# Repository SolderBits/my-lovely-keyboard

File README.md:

# My Lovely Keyboard

My Lovely Keyboard is a custom 75% mechanical keyboard with a hot-swap MX PCB,  rotary encoders with push buttons, and 3D-printed parts. The build pairs Akko Creamy Cyan clicky switches with SoulCat Cowgirl keycaps for the extra girly touch.

## PCB

The design uses a Pro Micro nRF52840 development board, four 74HC595 shift registers, and 1N4148 switching diodes for the key matrix. Jerrzi MX hot-swap sockets let you swap individual switches without desoldering them.

The hardware plan also includes a single-cell LiPo with a TP4056 charging module.

### Schematic and Board layout

### PCB renders

## Case

The build includes 3D-printed parts and SSS Fourwrap V2 PCB screw-in stabilizers. The stabilizer kit includes four 2U wires and wires for both 6.25U and 7U spacebars.

## Bill of Materials

| Part | Purpose | Purchase quantity | Total (INR) | Total (USD, approx.) |
|---|---|---:|---:|---:|
| [Akko Creamy Cyan switches](https://stackskb.com/store/akko-creamy-cyan-switch-pack-of-45-pre-order/) | Clicky MX switches | 2 packs of 45 | ₹2,598.00 | $28.00 |
| [Jerrzi MX hot-swap sockets](https://neomacro.in/products/jerrzi-mx-hotswap-sockets) | Removable switch mounting | 9 packs of 10 | ₹450.00 | $4.85 |
| [Pro Micro nRF52840](https://robu.in/product/promicro-nrf52840-development-board/) | Main controller | 1 | ₹899.00 | $9.69 |
| [74HC595 shift register](https://robocraze.com/products/8-bit-serial-to-parallel-shift-register-ic-74hc595) | Expand digital outputs | 4 | ₹60.00 | $0.65 |
| [3.7 V 10,000 mAh LiPo](https://makerbazar.in/products/single-cell-3-7v-10000mah-lipo-battery) | Battery power, variant without BMS or wires | 1 | ₹349.00 | $3.76 |
| [TP4056 1 A module](https://makerbazar.in/products/tp4056-1a-li-ion-lithium-battery-charging-module?variant=45459125567728) | Single-cell charging | 1 | ₹18.00 | $0.19 |
| [Hongyan EC11H rotary encoders](https://robu.in/product/hongyan-ec11h-7ce20p1zy15f7-rotary-encoder-with-push-button-switch-vertical-plug-in-5-pin/) | Rotary and push-button inputs | 2 | ₹116.00 | $1.25 |
| [SS-12D00 1P2T slide switches](https://robu.in/product/1-month-warranty-255/) | Slide switches | 6 | ₹11.34 | $0.12 |
| [SSS Fourwrap V2 stabilizers](https://neomacro.in/products/sss-fourwrap-v2-stabilizers) | Support wider keys | 1 kit | ₹1,059.00 | $11.41 |
| [PCB fabrication](https://jlcpcb.com/) | Custom keyboard PCB | 1 order | ₹3,692.77 | $39.80 |
| [1N4148 switching diodes](https://robu.in/product/1n4148-1w-zener-diode-pack-of-50/) | Key matrix isolation | 120 | ₹128.00 | $1.38 |
| [SoulCat Cowgirl keycaps](https://neomacro.in/products/soulcat-cowgirl-keycaps-pre-order) | 141-piece MOA-profile PBT keycap set | 1 set | ₹2,039.00 | $21.97 |
| 3D-printed parts | Mechanical assembly |  | |  |
| **Shipping ** | | | **₹119.81** | **$1.29** |
| **Total ** | | | **₹11,539.92** | **$124.37** |

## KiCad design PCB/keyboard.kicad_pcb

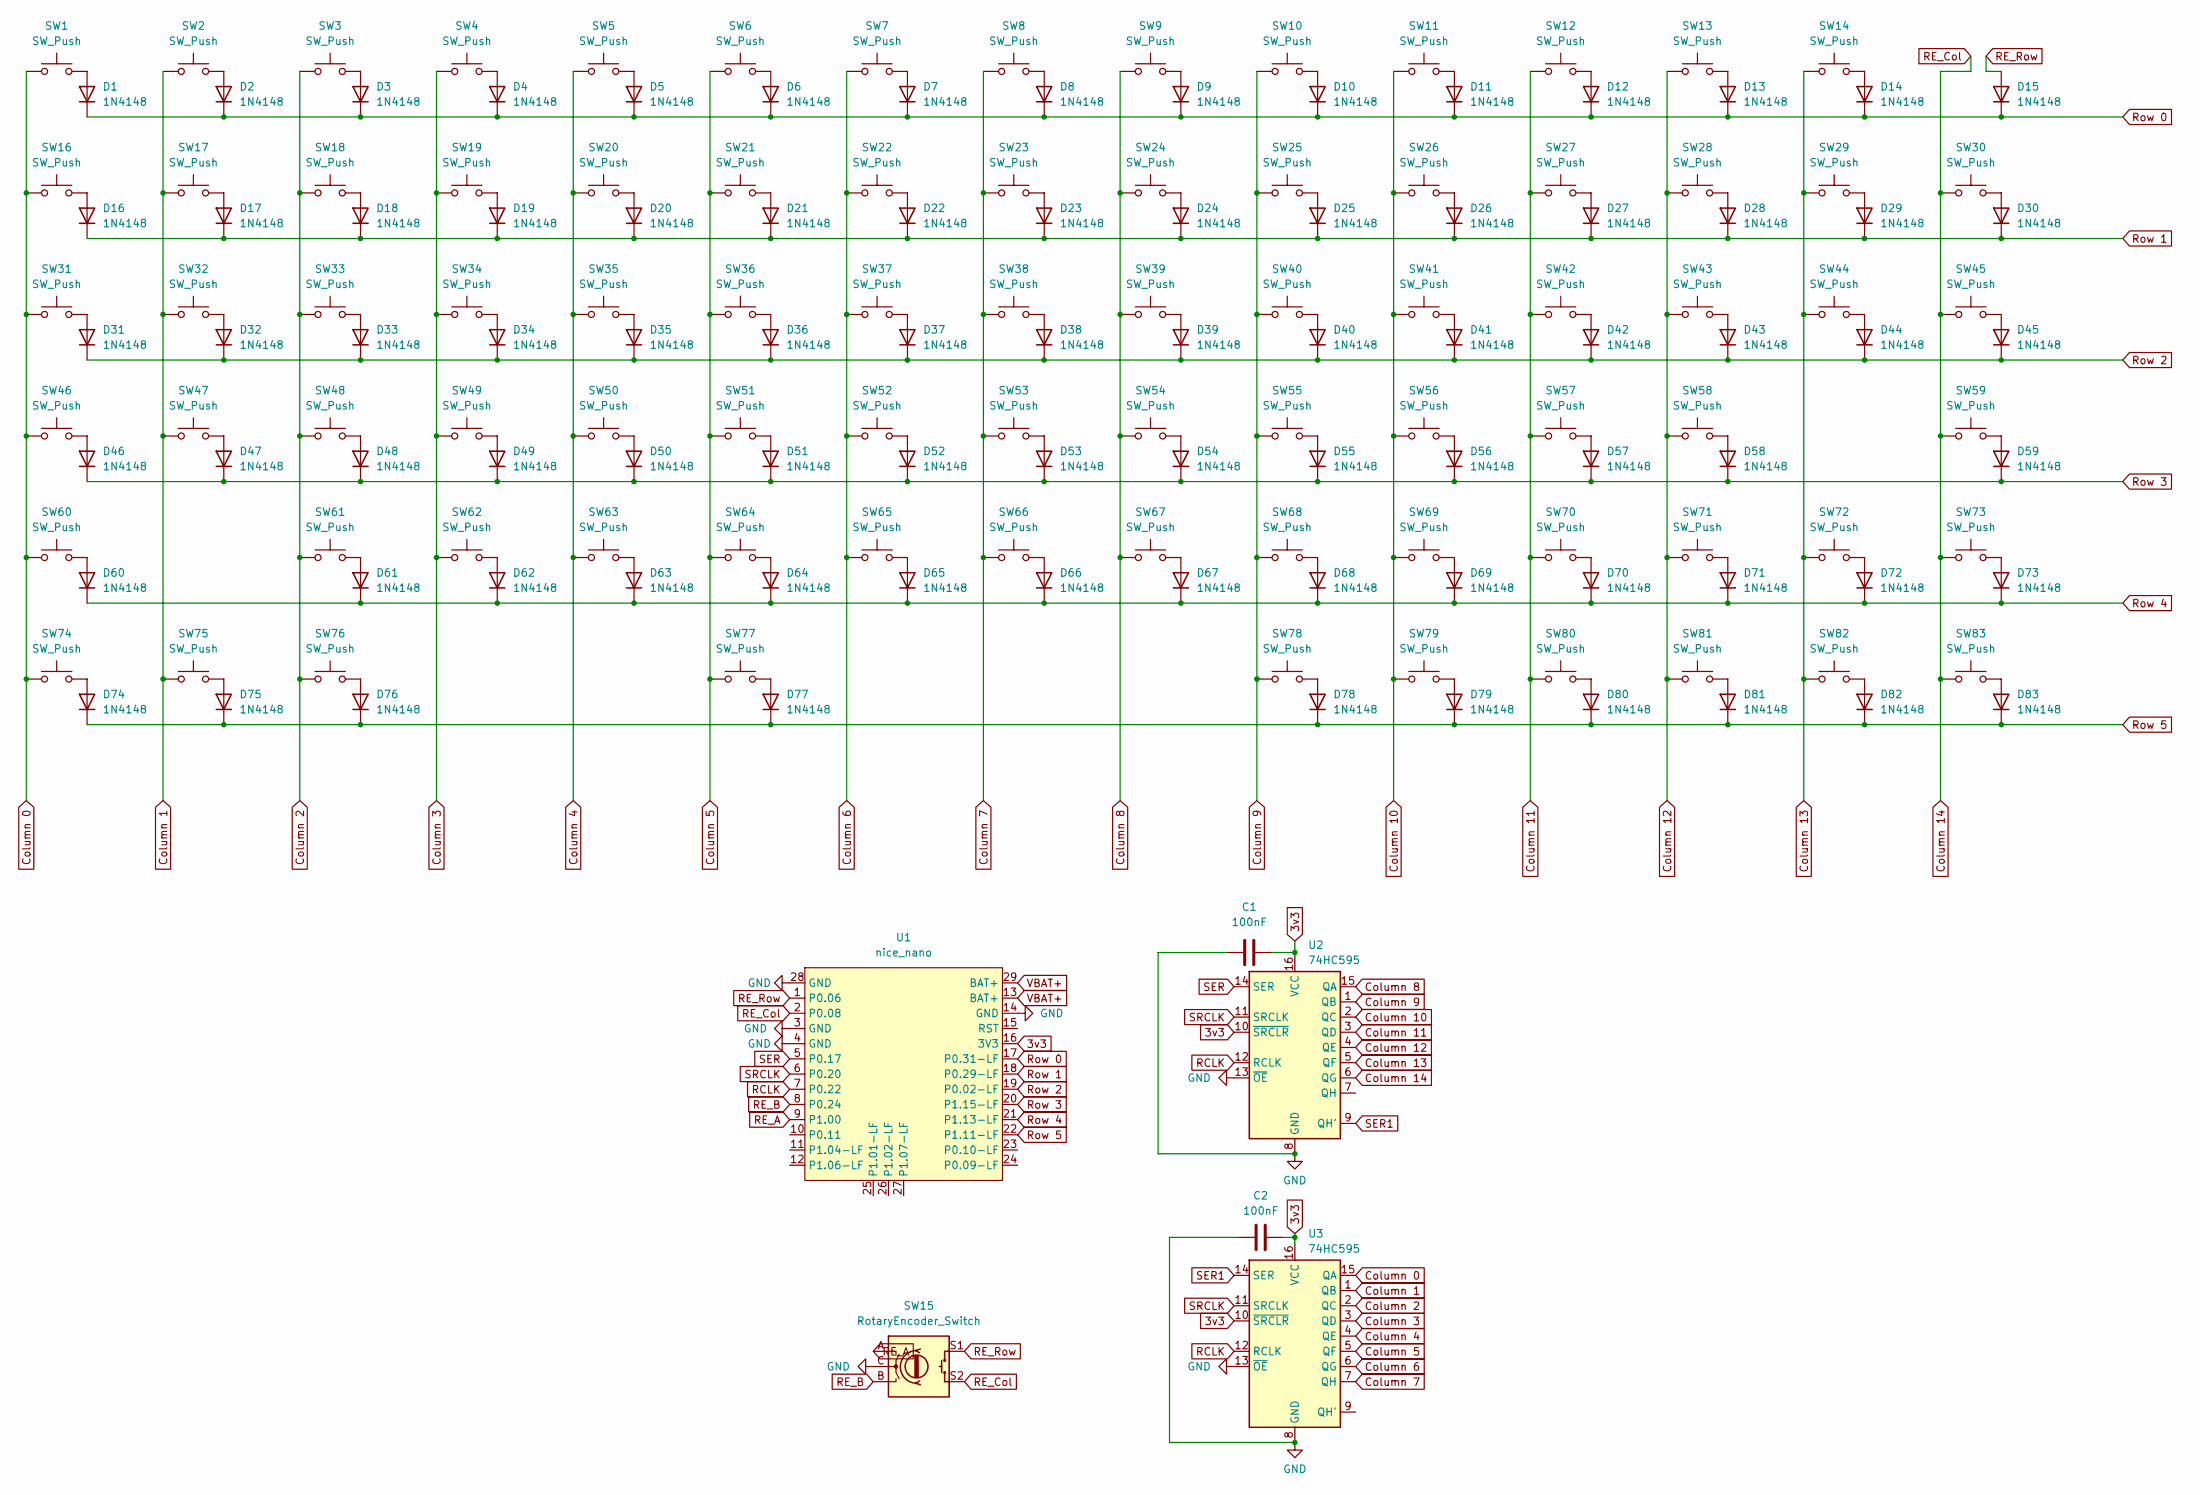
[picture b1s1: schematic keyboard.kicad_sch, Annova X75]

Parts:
C1, C2: 100nF; C_Disc_D3.0mm_W1.6mm_P2.50mm
D1, D2, D3, D4, D5, D6, D7, D8, D9, D10, D11, D12, D13, D14, D15, D16, D17, D18, D19, D20, D21, D22, D23, D24, D25, D26, D27, D28, D29, D30, D31, D32, D33, D34, D35, D36, D37, D38, D39, D40, D41, D42, D43, D44, D45, D46, D47, D48, D49, D50, D51, D52, D53, D54, D55, D56, D57, D58, D59, D60, D61, D62, D63, D64, D65, D66, D67, D68, D69, D70, D71, D72, D73, D74, D75, D76, D77, D78, D79, D80, D81, D82, D83: 1N4148; D_DO-35_SOD27_P7.62mm_Horizontal
SW1, SW2, SW3, SW4, SW5, SW6, SW7, SW8, SW9, SW10, SW11, SW12, SW13, SW14, SW16, SW17, SW18, SW19, SW20, SW21, SW22, SW23, SW24, SW25, SW26, SW27, SW28, SW30, SW32, SW33, SW34, SW35, SW36, SW37, SW38, SW39, SW40, SW41, SW42, SW43, SW45, SW47, SW48, SW49, SW50, SW51, SW52, SW53, SW54, SW55, SW56, SW57, SW59, SW61, SW62, SW63, SW64, SW65, SW66, SW67, SW68, SW69, SW70, SW72, SW73, SW78, SW79, SW80, SW81, SW82, SW83: SW_Push; SW_Hotswap_Kailh_MX_Plated_1.00u_With_Switch
SW15: RotaryEncoder_Switch; Encoder_EC11_MX_Combo
SW29: SW_Push; SW_Hotswap_Kailh_MX_Plated_2.00u_With_Switch
SW31, SW44: SW_Push; SW_Hotswap_Kailh_MX_Plated_1.50u_With_Switch
SW46, SW71: SW_Push; SW_Hotswap_Kailh_MX_Plated_1.75u_With_Switch
SW58, SW60: SW_Push; SW_Hotswap_Kailh_MX_Plated_2.25u_With_Switch
SW74, SW75, SW76: SW_Push; SW_Hotswap_Kailh_MX_Plated_1.25u_With_Switch
SW77: SW_Push; SW_Hotswap_Kailh_MX_Plated_6.25u_With_Switch
U1: nice_nano; SuperMini NRF52840
U2, U3: 74HC595; DIP-16_W7.62mm

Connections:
3v3: C1.1, C2.1, U1.16 (3V3), U2.10 (~SRCLR), U2.16 (VCC), U3.10 (~SRCLR), U3.16 (VCC)
Column 0: SW1.1, SW16.1, SW31.1, SW46.1, SW60.1, SW74.1, U3.15 (QA)
Column 1: SW2.1, SW17.1, SW32.1, SW47.1, SW75.1, U3.1 (QB)
Column 2: SW3.1, SW18.1, SW33.1, SW48.1, SW61.1, SW76.1, U3.2 (QC)
Column 3: SW4.1, SW19.1, SW34.1, SW49.1, SW62.1, U3.3 (QD)
Column 4: SW5.1, SW20.1, SW35.1, SW50.1, SW63.1, U3.4 (QE)
Column 5: SW6.1, SW21.1, SW36.1, SW51.1, SW64.1, SW77.1, U3.5 (QF)
Column 6: SW7.1, SW22.1, SW37.1, SW52.1, SW65.1, U3.6 (QG)
Column 7: SW8.1, SW23.1, SW38.1, SW53.1, SW66.1, U3.7 (QH)
Column 8: SW9.1, SW24.1, SW39.1, SW54.1, SW67.1, U2.15 (QA)
Column 9: SW10.1, SW25.1, SW40.1, SW55.1, SW68.1, SW78.1, U2.1 (QB)
Column 10: SW11.1, SW26.1, SW41.1, SW56.1, SW69.1, SW79.1, U2.2 (QC)
Column 11: SW12.1, SW27.1, SW42.1, SW57.1, SW70.1, SW80.1, U2.3 (QD)
Column 12: SW13.1, SW28.1, SW43.1, SW58.1, SW71.1, SW81.1, U2.4 (QE)
Column 13: SW14.1, SW29.1, SW44.1, SW72.1, SW82.1, U2.5 (QF)
Column 14: SW15.S2, SW30.1, SW45.1, SW59.1, SW73.1, SW83.1, U1.2 (P0.08), U2.6 (QG)
GND: C1.2, C2.2, SW15.C, U1.3 (GND), U1.4 (GND), U1.14 (GND), U1.28 (GND), U2.8 (GND), U2.13 (~OE), U3.8 (GND), U3.13 (~OE)
unnamed: D1.2 (A), SW1.2
unnamed: D2.2 (A), SW2.2
unnamed: D3.2 (A), SW3.2
unnamed: D4.2 (A), SW4.2
unnamed: D5.2 (A), SW5.2
unnamed: D6.2 (A), SW6.2
unnamed: D7.2 (A), SW7.2
unnamed: D8.2 (A), SW8.2
unnamed: D9.2 (A), SW9.2
unnamed: D10.2 (A), SW10.2
unnamed: D11.2 (A), SW11.2
unnamed: D12.2 (A), SW12.2
unnamed: D13.2 (A), SW13.2
unnamed: D14.2 (A), SW14.2
unnamed: D16.2 (A), SW16.2
unnamed: D17.2 (A), SW17.2
unnamed: D18.2 (A), SW18.2
unnamed: D19.2 (A), SW19.2
unnamed: D20.2 (A), SW20.2
unnamed: D21.2 (A), SW21.2
unnamed: D22.2 (A), SW22.2
unnamed: D23.2 (A), SW23.2
unnamed: D24.2 (A), SW24.2
unnamed: D25.2 (A), SW25.2
unnamed: D26.2 (A), SW26.2
unnamed: D27.2 (A), SW27.2
unnamed: D28.2 (A), SW28.2
unnamed: D29.2 (A), SW29.2
unnamed: D30.2 (A), SW30.2
unnamed: D31.2 (A), SW31.2
unnamed: D32.2 (A), SW32.2
unnamed: D33.2 (A), SW33.2
unnamed: D34.2 (A), SW34.2
unnamed: D35.2 (A), SW35.2
unnamed: D36.2 (A), SW36.2
unnamed: D37.2 (A), SW37.2
unnamed: D38.2 (A), SW38.2
unnamed: D39.2 (A), SW39.2
unnamed: D40.2 (A), SW40.2
unnamed: D41.2 (A), SW41.2
unnamed: D42.2 (A), SW42.2
unnamed: D43.2 (A), SW43.2
unnamed: D44.2 (A), SW44.2
unnamed: D45.2 (A), SW45.2
unnamed: D46.2 (A), SW46.2
unnamed: D47.2 (A), SW47.2
unnamed: D48.2 (A), SW48.2
unnamed: D49.2 (A), SW49.2
unnamed: D50.2 (A), SW50.2
unnamed: D51.2 (A), SW51.2
unnamed: D52.2 (A), SW52.2
unnamed: D53.2 (A), SW53.2
unnamed: D54.2 (A), SW54.2
unnamed: D55.2 (A), SW55.2
unnamed: D56.2 (A), SW56.2
unnamed: D57.2 (A), SW57.2
unnamed: D58.2 (A), SW58.2
unnamed: D59.2 (A), SW59.2
unnamed: D60.2 (A), SW60.2
unnamed: D61.2 (A), SW61.2
unnamed: D62.2 (A), SW62.2
unnamed: D63.2 (A), SW63.2
unnamed: D64.2 (A), SW64.2
unnamed: D65.2 (A), SW65.2
unnamed: D66.2 (A), SW66.2
unnamed: D67.2 (A), SW67.2
unnamed: D68.2 (A), SW68.2
unnamed: D69.2 (A), SW69.2
unnamed: D70.2 (A), SW70.2
unnamed: D71.2 (A), SW71.2
unnamed: D72.2 (A), SW72.2
unnamed: D73.2 (A), SW73.2
unnamed: D74.2 (A), SW74.2
unnamed: D75.2 (A), SW75.2
unnamed: D76.2 (A), SW76.2
unnamed: D77.2 (A), SW77.2
unnamed: D78.2 (A), SW78.2
unnamed: D79.2 (A), SW79.2
unnamed: D80.2 (A), SW80.2
unnamed: D81.2 (A), SW81.2
unnamed: D82.2 (A), SW82.2
unnamed: D83.2 (A), SW83.2
RCLK: U1.7 (P0.22), U2.12 (RCLK), U3.12 (RCLK)
RE_A: SW15.A, U1.9 (P1.00)
RE_B: SW15.B, U1.8 (P0.24)
RE_Row: D15.2 (A), SW15.S1, U1.1 (P0.06)
Row 0: D1.1 (K), D2.1 (K), D3.1 (K), D4.1 (K), D5.1 (K), D6.1 (K), D7.1 (K), D8.1 (K), D9.1 (K), D10.1 (K), D11.1 (K), D12.1 (K), D13.1 (K), D14.1 (K), D15.1 (K), U1.17 (P0.31-LF)
Row 1: D16.1 (K), D17.1 (K), D18.1 (K), D19.1 (K), D20.1 (K), D21.1 (K), D22.1 (K), D23.1 (K), D24.1 (K), D25.1 (K), D26.1 (K), D27.1 (K), D28.1 (K), D29.1 (K), D30.1 (K), U1.18 (P0.29-LF)
Row 2: D31.1 (K), D32.1 (K), D33.1 (K), D34.1 (K), D35.1 (K), D36.1 (K), D37.1 (K), D38.1 (K), D39.1 (K), D40.1 (K), D41.1 (K), D42.1 (K), D43.1 (K), D44.1 (K), D45.1 (K), U1.19 (P0.02-LF)
Row 3: D46.1 (K), D47.1 (K), D48.1 (K), D49.1 (K), D50.1 (K), D51.1 (K), D52.1 (K), D53.1 (K), D54.1 (K), D55.1 (K), D56.1 (K), D57.1 (K), D58.1 (K), D59.1 (K), U1.20 (P1.15-LF)
Row 4: D60.1 (K), D61.1 (K), D62.1 (K), D63.1 (K), D64.1 (K), D65.1 (K), D66.1 (K), D67.1 (K), D68.1 (K), D69.1 (K), D70.1 (K), D71.1 (K), D72.1 (K), D73.1 (K), U1.21 (P1.13-LF)
Row 5: D74.1 (K), D75.1 (K), D76.1 (K), D77.1 (K), D78.1 (K), D79.1 (K), D80.1 (K), D81.1 (K), D82.1 (K), D83.1 (K), U1.22 (P1.11-LF)
SER: U1.5 (P0.17), U2.14 (SER)
SER1: U2.9 (QH'), U3.14 (SER)
SRCLK: U1.6 (P0.20), U2.11 (SRCLK), U3.11 (SRCLK)
VBAT+: U1.13 (BAT+), U1.29 (BAT+)

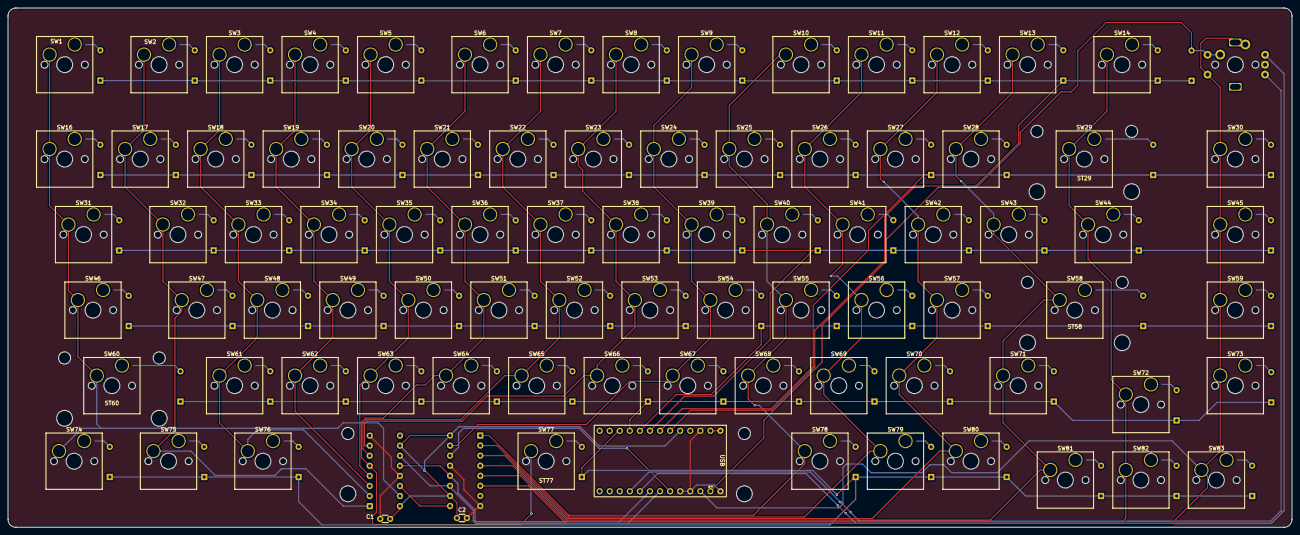
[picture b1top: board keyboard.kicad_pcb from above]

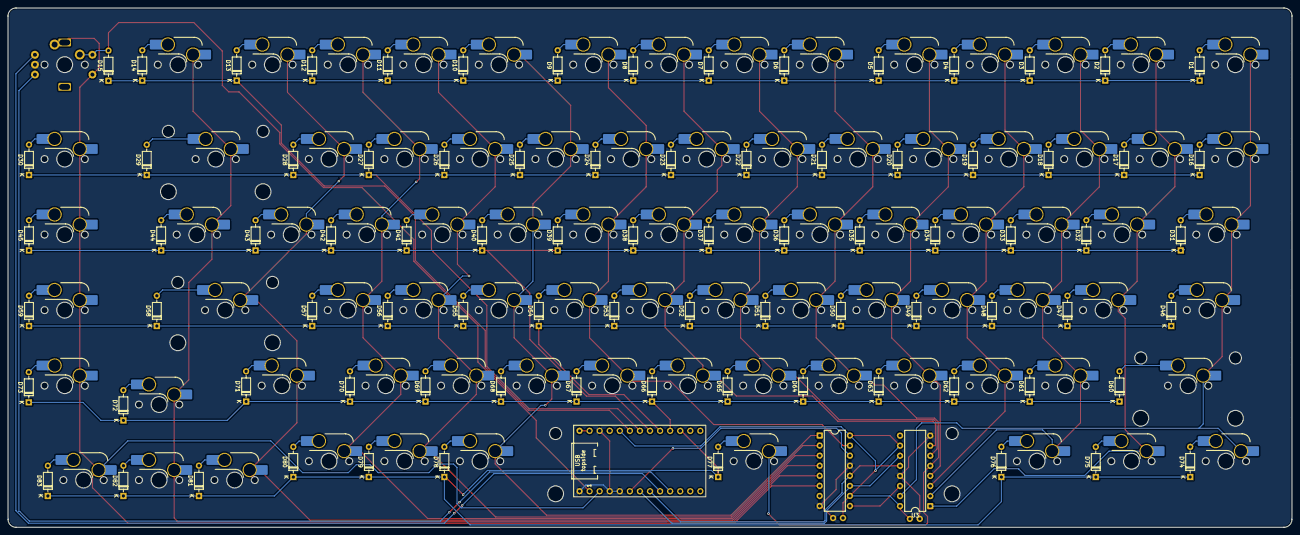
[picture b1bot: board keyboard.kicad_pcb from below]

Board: 2 copper layers, 323.9 x 131.0 mm, 175 parts (86 on the bottom side), 113 nets.

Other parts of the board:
ST29, ST58, ST60: Stabilizer_Cherry_MX_2.00u
ST77: Stabilizer_Cherry_MX_6.25u

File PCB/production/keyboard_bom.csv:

Designator,Footprint,Quantity,Value,LCSC Part #
"C1, C2",C_Disc_D3.0mm_W1.6mm_P2.50mm,2,100nF,
"D1, D10, D11, D12, D13, D14, D15, D16, D17, D18, D19, D2, D20, D21, D22, D23, D24, D25, D26, D27, D28, D29, D3, D30, D31, D32, D33, D34, D35, D36, D37, D38, D39, D4, D40, D41, D42, D43, D44, D45, D46, D47, D48, D49, D5, D50, D51, D52, D53, D54, D55, D56, D57, D58, D59, D6, D60, D61, D62, D63, D64, D65, D66, D67, D68, D69, D7, D70, D71, D72, D73, D74, D75, D76, D77, D78, D79, D8, D80, D81, D82, D83, D9",D_DO-35_SOD27_P7.62mm_Horizontal,83,1N4148,
"SW1, SW10, SW11, SW12, SW13, SW14, SW16, SW17, SW18, SW19, SW2, SW20, SW21, SW22, SW23, SW24, SW25, SW26, SW27, SW28, SW3, SW30, SW32, SW33, SW34, SW35, SW36, SW37, SW38, SW39, SW4, SW40, SW41, SW42, SW43, SW45, SW47, SW48, SW49, SW5, SW50, SW51, SW52, SW53, SW54, SW55, SW56, SW57, SW59, SW6, SW61, SW62, SW63, SW64, SW65, SW66, SW67, SW68, SW69, SW7, SW70, SW72, SW73, SW78, SW79, SW8, SW80, SW81, SW82, SW83, SW9",SW_Hotswap_Kailh_MX_Plated_1.00u_With_Switch,71,SW_Push,
SW15,Encoder_EC11_MX_Combo,1,RotaryEncoder_Switch,
SW29,SW_Hotswap_Kailh_MX_Plated_2.00u_With_Switch,1,SW_Push,
"SW31, SW44",SW_Hotswap_Kailh_MX_Plated_1.50u_With_Switch,2,SW_Push,
"SW46, SW71",SW_Hotswap_Kailh_MX_Plated_1.75u_With_Switch,2,SW_Push,
"SW58, SW60",SW_Hotswap_Kailh_MX_Plated_2.25u_With_Switch,2,SW_Push,
"SW74, SW75, SW76",SW_Hotswap_Kailh_MX_Plated_1.25u_With_Switch,3,SW_Push,
SW77,SW_Hotswap_Kailh_MX_Plated_6.25u_With_Switch,1,SW_Push,
"U2, U3",DIP-16_W7.62mm,2,74HC595,
